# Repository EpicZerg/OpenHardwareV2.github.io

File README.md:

OpenHardwareV2
========================
This Project Provides tons of Free Board/Schematic Designs.
See Full List at: epiczerg.github.io

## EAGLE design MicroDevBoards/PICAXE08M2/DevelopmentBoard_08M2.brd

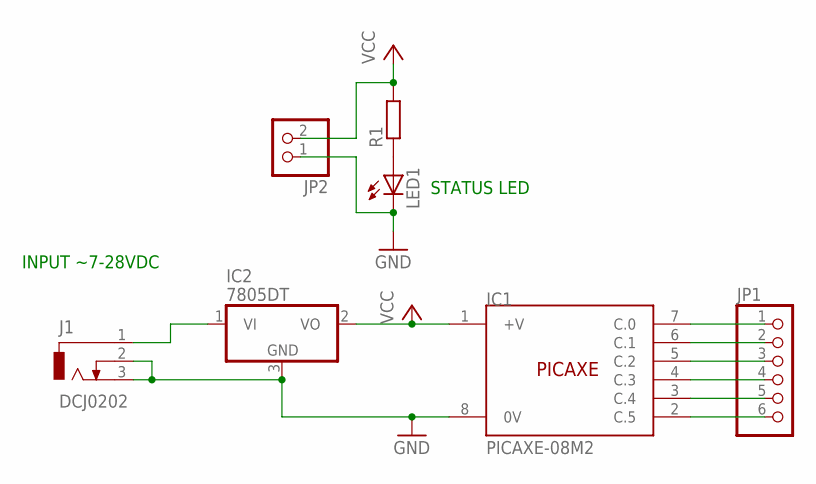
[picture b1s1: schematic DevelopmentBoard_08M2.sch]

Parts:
IC1: PICAXE-08M2; SOIC8
IC2: 7805DT; TO252
J1: DCJ0202
JP1: PINHD-1X6; 1X06
JP2: PINHD-1X2; 1X02
LED1: LEDCHIPLED_1206; CHIPLED_1206
R1: R-EU_R1206; R1206

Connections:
GND: IC1.8 (0V), IC2.3 (GND), J1.2, J1.3, JP2.1, LED1.C
unnamed: IC2.1 (VI), J1.1
unnamed: LED1.A, R1.1
unnamed: IC1.7 (C.0), JP1.1
unnamed: IC1.6 (C.1), JP1.2
unnamed: IC1.5 (C.2), JP1.3
unnamed: IC1.4 (C.3), JP1.4
unnamed: IC1.3 (C.4), JP1.5
unnamed: IC1.2 (C.5), JP1.6
VCC: IC1.1 (+V), IC2.2 (VO), JP2.2, R1.2

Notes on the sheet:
INPUT ~7-28VDC
STATUS LED

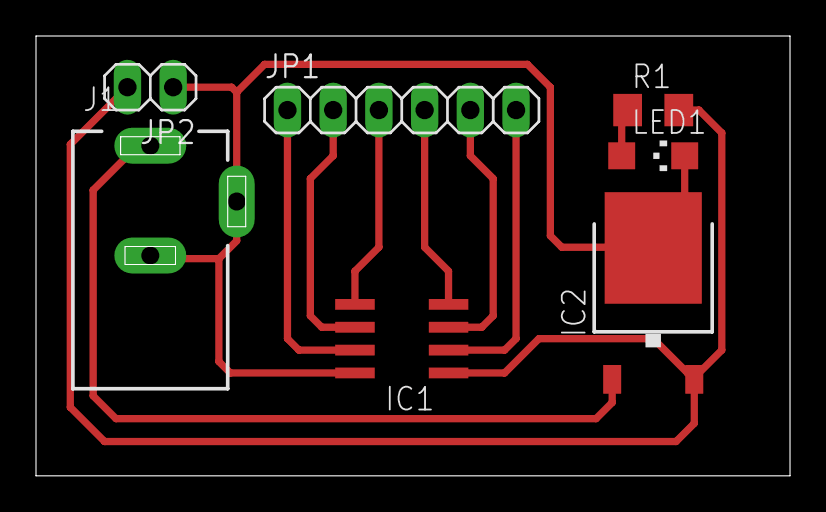
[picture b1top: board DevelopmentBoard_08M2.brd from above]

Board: 2 copper layers, 41.9 x 24.4 mm, 7 parts (0 on the bottom side), 10 nets.

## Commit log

2014-02-01 Added Website
2014-02-01 Added Libraries
    Libraries by chiengineer
2014-02-01 Added PICAXE08M2 Development Board
    Layout and Schematic
